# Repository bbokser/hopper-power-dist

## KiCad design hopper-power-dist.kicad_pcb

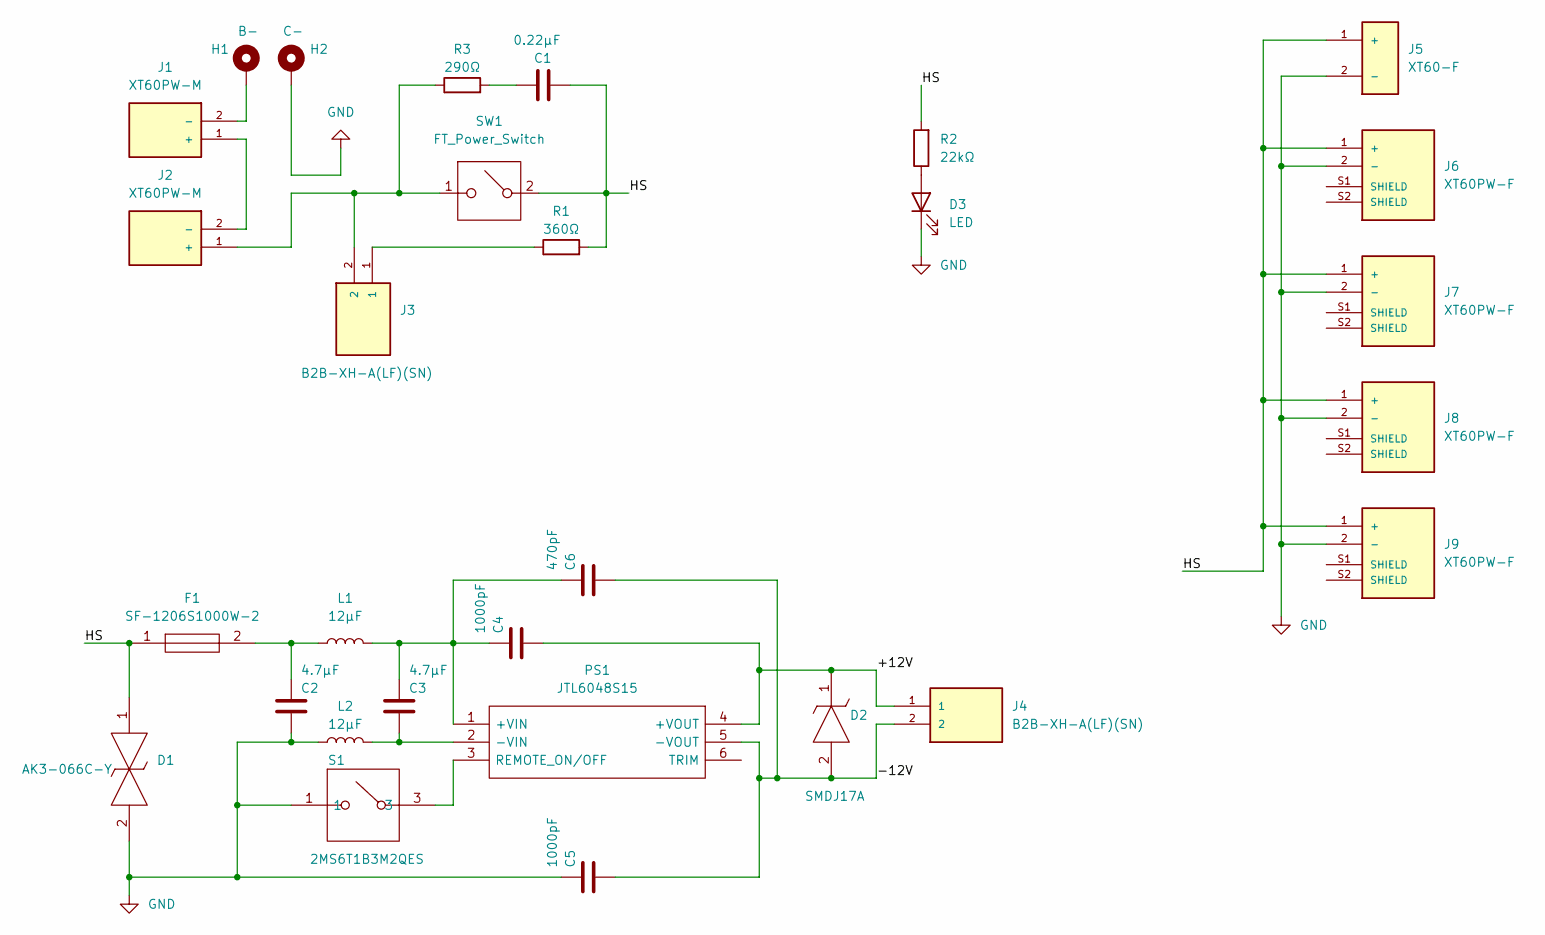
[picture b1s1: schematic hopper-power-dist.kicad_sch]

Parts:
C1: 0.22μF; C_1206_3216Metric
C2: 4.7μF; CAPC3225X270N
C3: 4.7μF; C_0805_2012Metric
C4, C5: 1000pF; C_1206_3216Metric
C6: 470pF; C_1206_3216Metric
D1: AK3-066C-Y; AK3066CY; Mouser Part Number 576-AK3-066C-Y
D2: SMDJ17A; DIOM7959X262N; Manufacturer_Part_Number SMDJ17A
D3: LED; LED_0603_1608Metric
F1: SF-1206S1000W-2; FUSC3216X123N; Mouser Part Number 652-SF-1206S1000W-2
H1: B-; MountingHole_4.3mm_M4_Pad_Via
H2: C-; MountingHole_4.3mm_M4_Pad_Via
J1, J2: XT60PW-M; AMASS_XT60PW-M; PARTREV V1.2
J3, J4: B2B-XH-A(LF)(SN); JST_B2B-XH-A(LF)(SN)
J5: XT60-F; AMASS_XT60-F; PARTREV 1.2
J6, J7, J8, J9: XT60PW-F; AMASS_XT60PW-F; PARTREV V1.2
L1, L2: 12μF; LPS6235123MRC
PS1: JTL6048S15; Mouser Part Number 209-JTL6048S15
R1: 360Ω; AC03000003600JAC00
R2: 22kΩ; R_0603_1608Metric_Pad0.98x0.95mm_HandSolder
R3: 290Ω; R_2512_6332Metric
S1: 2MS6T1B3M2QES; Mouser Part Number 118-2MS6T1B3M2QES
SW1: FT_Power_Switch; FT Power Switch

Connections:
/+12V: C4.2, D2.1, J4.1, PS1.4 (+VOUT)
/-12V: C5.2, C6.2, D2.2, J4.2, PS1.5 (-VOUT)
/HS: C1.2, D1.1, F1.1, J5.1 (+), J6.1 (+), J7.1 (+), J8.1 (+), J9.1 (+), R1.2, R2.2, SW1.2
GND: C2.2, C5.1, D1.2, D3.1 (K), H2.1, J5.2 (-), J6.2 (-), J7.2 (-), J8.2 (-), J9.2 (-), L2.1, S1.1
unnamed: C1.1, R3.2
unnamed: C2.1, F1.2, L1.1
unnamed: C3.1, C4.1, C6.1, L1.2, PS1.1 (+VIN)
unnamed: C3.2, L2.2, PS1.2 (-VIN)
unnamed: D3.2 (A), R2.1
unnamed: H1.1, J1.2 (-)
unnamed: J1.1 (+), J2.2 (-)
unnamed: J2.1 (+), J3.2, R3.1, SW1.1
unnamed: J3.1, R1.1
unnamed: PS1.3 (REMOTE_ON/OFF), S1.3

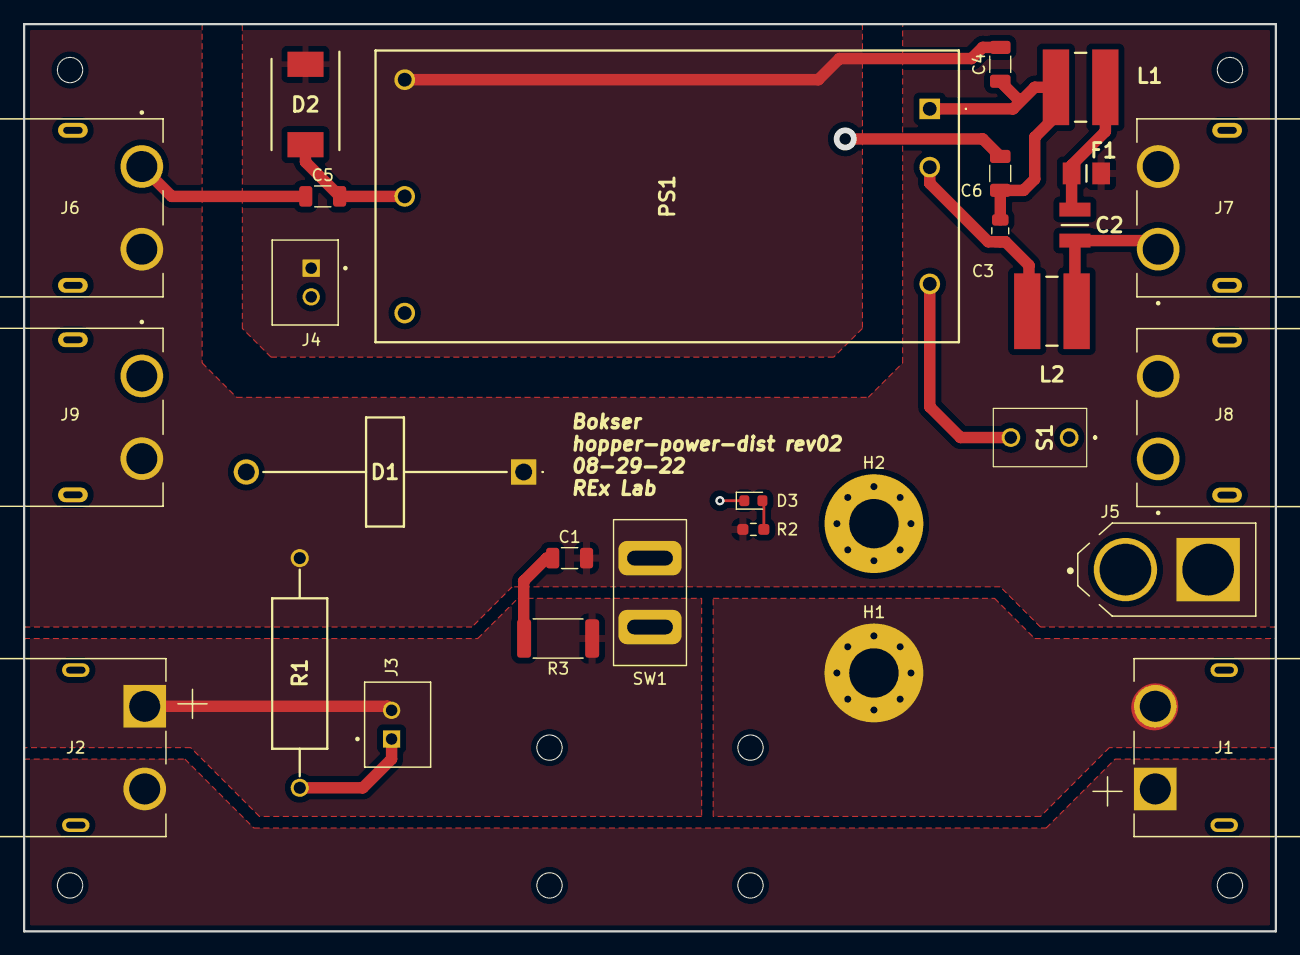
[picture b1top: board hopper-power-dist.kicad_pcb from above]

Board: 2 copper layers, 109.0 x 79.0 mm, 30 parts (0 on the bottom side), 14 nets.

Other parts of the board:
REF: MountingHole_2.2mm_M2

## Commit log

2022-07-13 Create schematic
2022-07-15 Initialize PCB, update gitignore
2022-07-17 Create basic PCB layout
2022-07-17 Update BoM
2022-07-17 Remove backup folder from git tracking
2022-07-18 Fix schematic and update 3d models
2022-07-20 Changed precharge resistor, routed PCB traces and updated 3D models
2022-07-24 Improved PCB design and completed DRC
2022-07-25 Moved BEC JST connector to be more accessible
2022-08-21 Start rev02, fix minor mistakes and add xt60pw-m series
2022-08-21 Replace DC-DC converter with thru-hole version and clean up
2022-08-23 Replaced DC-DC Converter and working on capacitor selection
2022-08-23 Further tweaks to v2 design
2022-08-29 Minor improvements made
2022-08-29 Added spark suppression and changed thermal reliefs to solid on high power pads
2023-03-11 Started rev03 design
2023-05-14 Add e-stop circuit
2023-06-12 Change estop circuit to 5V
